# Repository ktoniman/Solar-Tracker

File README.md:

Electrical Engineering Principles and Practices (E1111A) Project
a Y1S1 project to be improved

If time allows, next pcb iteration using copper pours

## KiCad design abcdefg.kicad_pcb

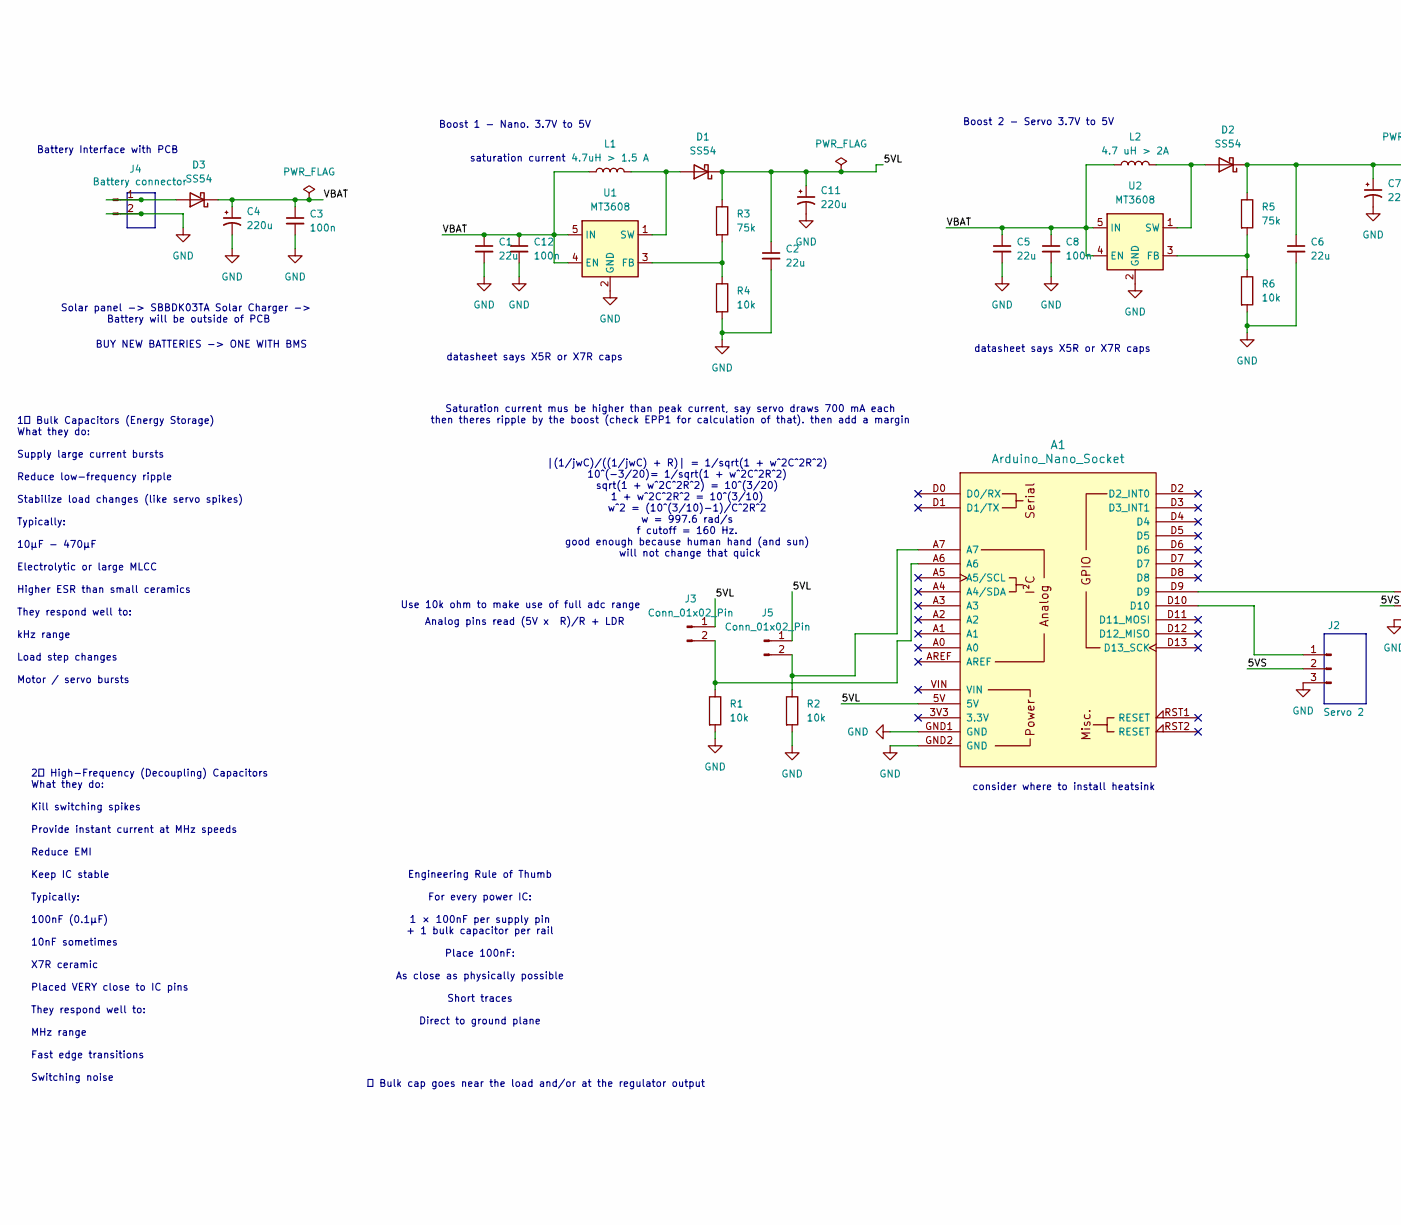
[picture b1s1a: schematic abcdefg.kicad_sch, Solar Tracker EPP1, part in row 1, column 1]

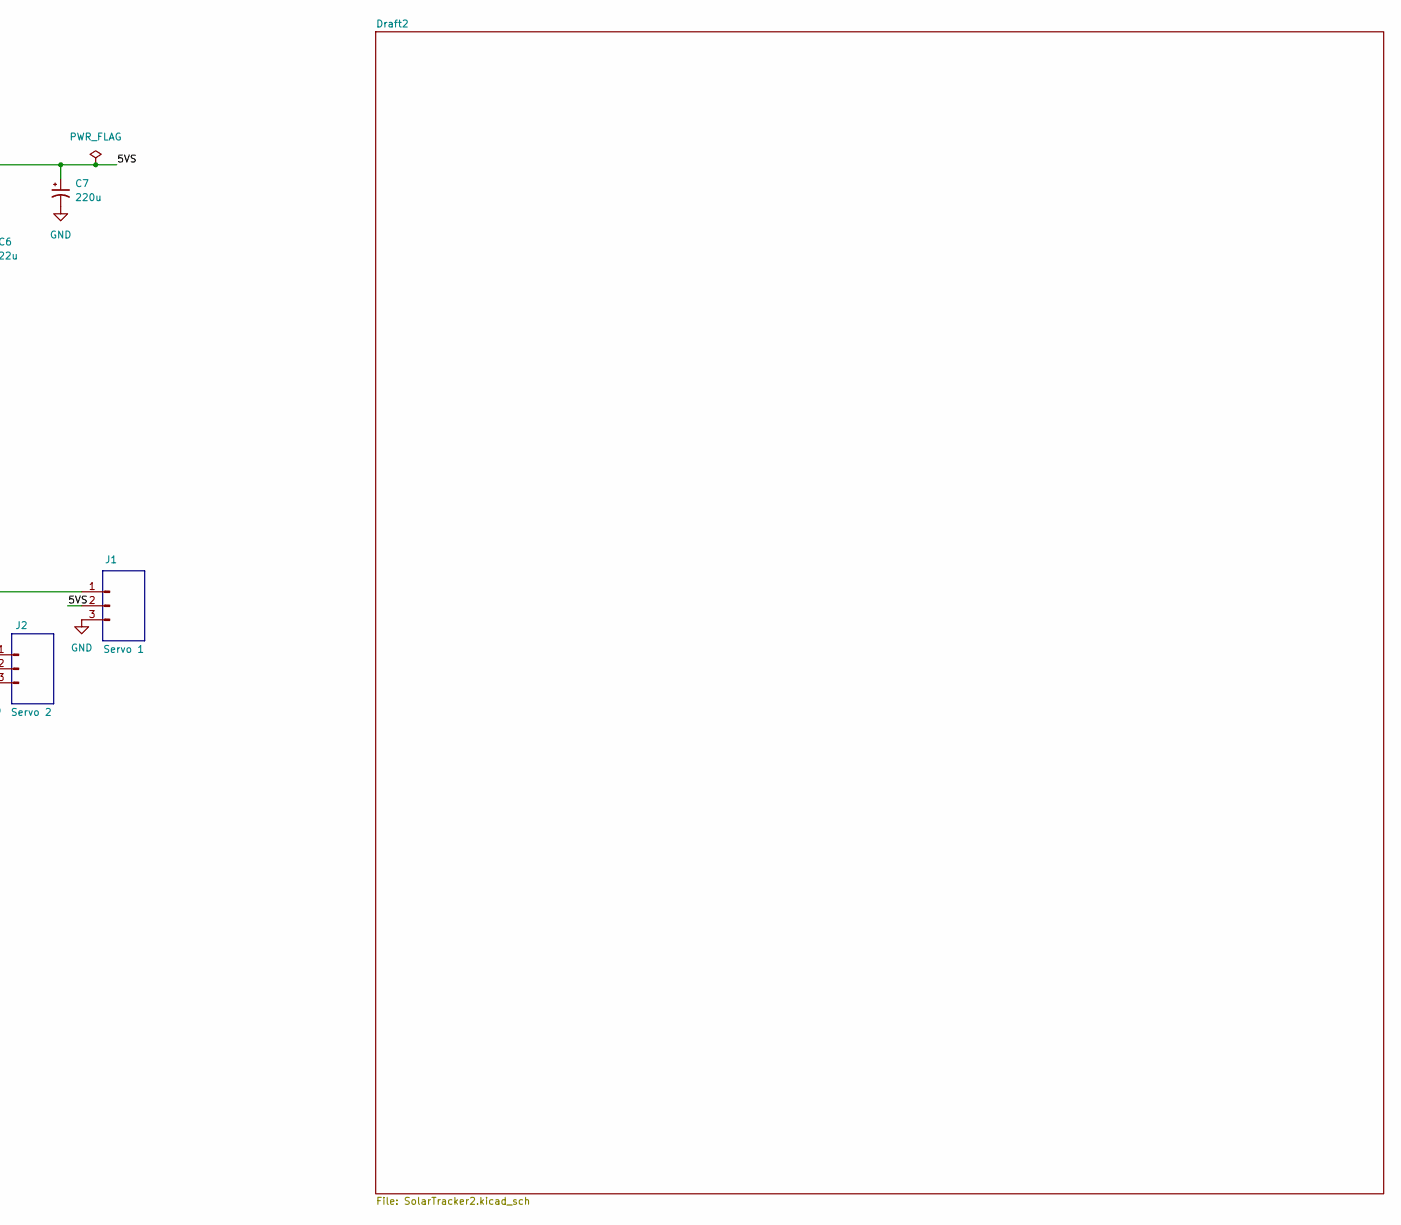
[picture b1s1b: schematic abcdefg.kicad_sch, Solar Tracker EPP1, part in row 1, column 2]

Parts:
A1: Arduino_Nano_Socket
C1, C2, C5, C6: 22u; C_0805_2012Metric
C3, C8, C12: 100n; C_0805_2012Metric
C4, C7, C11: 220u; CP_Elec_6.3x7.7
D1, D2, D3: SS54; D_SMA
J1: Servo 1; JST_XH_B3B-XH-A_1x03_P2.50mm_Vertical
J2: Servo 2; JST_XH_B3B-XH-A_1x03_P2.50mm_Vertical
J3, J5: Conn_01x02_Pin; JST_XH_B2B-XH-A_1x02_P2.50mm_Vertical
J4: Battery connector; JST_XH_B2B-XH-A_1x02_P2.50mm_Vertical
L1: 4.7uH > 1.5 A; L_Sunlord_SWPA8040S
L2: 4.7 uH > 2A; L_Sunlord_SWPA8040S
R1, R2, R4, R6: 10k; R_0805_2012Metric
R3, R5: 75k; R_0603_1608Metric
U1, U2: MT3608; SOT-23-6

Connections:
/5VL: A1.5V, C2.1, C11.1, D1.1 (K), J3.1, J5.1, R3.1
/5VS: C6.1, C7.1, D2.1 (K), J1.2, J2.2, R5.1
/VBAT: C1.1, C3.1, C4.1, C5.1, C8.1, C12.1, D3.1 (K), L1.1, L2.1, U1.4 (EN), U1.5 (IN), U2.4 (EN), U2.5 (IN)
GND: A1.GND1 (GND), A1.GND2 (GND), C1.2, C2.2, C3.2, C4.2, C5.2, C6.2, C7.2, C8.2, C11.2, C12.2, J1.3, J2.3, J4.2, R1.2, R2.2, R4.2, R6.2, U1.2 (GND), U2.2 (GND)
unnamed: D1.2 (A), L1.2, U1.1 (SW)
unnamed: D2.2 (A), L2.2, U2.1 (SW)
unnamed: D3.2 (A), J4.1
unnamed: A1.D9, J1.1
unnamed: A1.D10, J2.1
unnamed: A1.A6, J3.2, R1.1
unnamed: A1.A7, J5.2, R2.1
unnamed: R3.2, R4.1, U1.3 (FB)
unnamed: R5.2, R6.1, U2.3 (FB)

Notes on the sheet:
BUY NEW BATTERIES -> ONE WITH BMS
Solar panel -> SBBDK03TA Solar Charger -> Battery will be outside of PCB
Battery Interface with PCB
2️⃣ High-Frequency (Decoupling) Capacitors What they do: Kill switching spikes Provide instant current at MHz speeds Reduce EMI Keep IC stable Typically: 100nF (0.1µF) 10nF sometimes X7R ceramic Placed VERY close to IC pins They respond well to: MHz range Fast edge transitions Switching noise
1️⃣ Bulk Capacitors (Energy Storage) What they do: Supply large current bursts Reduce low-frequency ripple Stabilize load changes (like servo spikes) Typically: 10µF - 470µF Electrolytic or large MLCC Higher ESR than small ceramics They respond well to: kHz range Load step changes Motor / servo bur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
Use 10k ohm to make use of full adc range
Boost 2 - Servo 3.7V to 5V
datasheet says X5R or X7R caps
Saturation current mus be higher than peak current, say servo draws 700 mA each then theres ripple by the boost (check EPP1 for calculation of that). then add a margin
Analog pins read (5V x R)/R + LDR
saturation current
|(1/jwC)/((1/jwC) + R)| = 1/sqrt(1 + w^2C^2R^2) 10^(-3/20)= 1/sqrt(1 + w^2C^2R^2) sqrt(1 + w^2C^2R^2) = 10^(3/20) 1 + w^2C^2R^2 = 10^(3/10) w^2 = (10^(3/10)-1)/C^2R^2 w = 997.6 rad/s f cutoff = 160 Hz. good enough because human hand (and sun) will not change that quick
Engineering Rule of Thumb For every power IC: 1 × 100nF per supply pin + 1 bulk capacitor per rail Place 100nF: As close as physically possible Short traces Direct to ground plane
consider where to install heatsink
✅ Bulk cap goes near the load and/or at the regulator output
Boost 1 - Nano. 3.7V to 5V

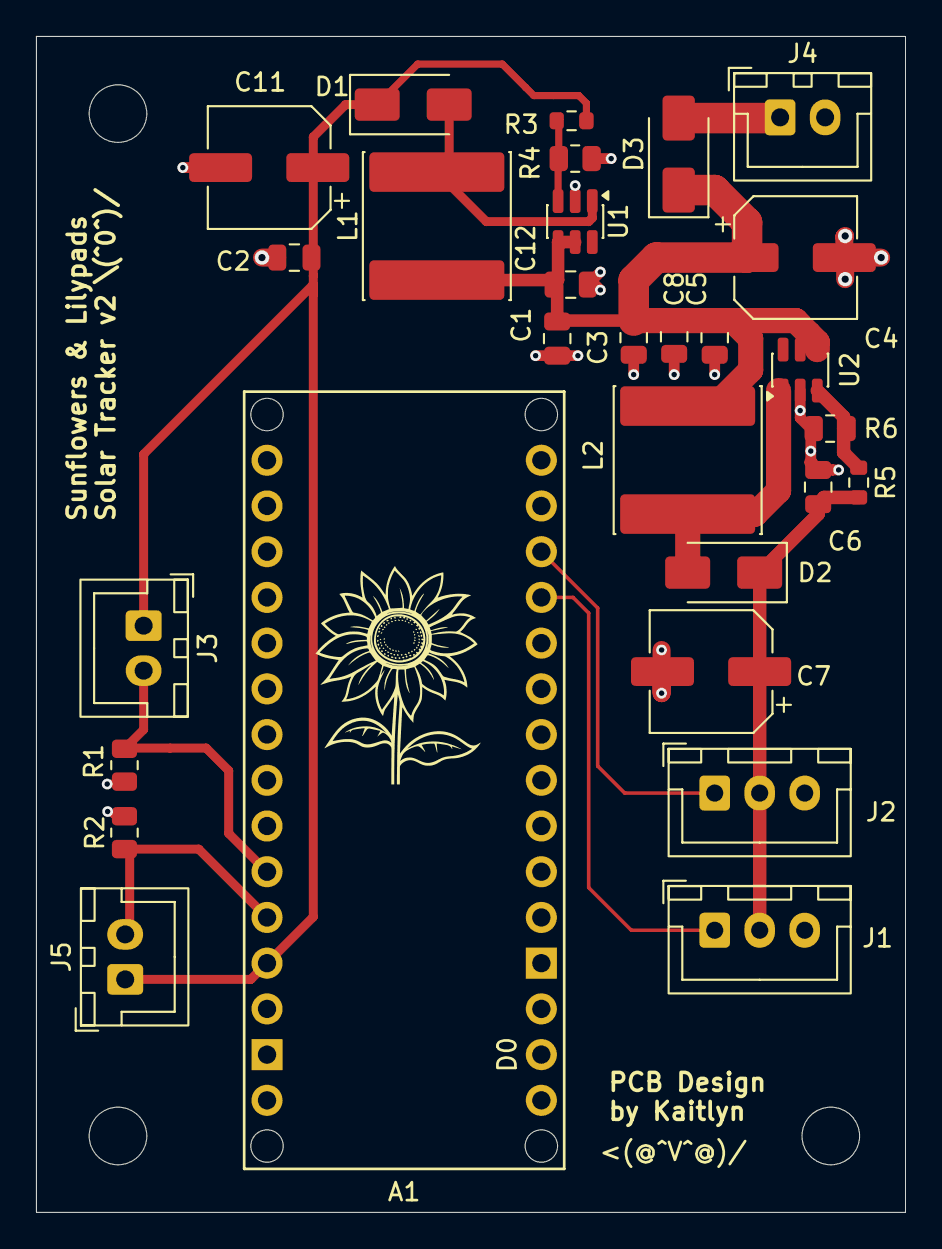
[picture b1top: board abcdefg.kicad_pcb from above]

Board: 2 copper layers, 48.3 x 65.3 mm, 29 parts (0 on the bottom side), 13 nets.

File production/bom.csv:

Designator,Footprint,Quantity,Value,LCSC Part #
A1,Arduino_Nano_Socket,1,Arduino_Nano_Socket,
"C1, C2, C5, C6",0805,4,22u,
"C11, C4, C7",CP_Elec_6.3x7.7,3,220u,
"C12, C3, C8",0805,3,100n,
"D1, D2, D3",D_SMA,3,SS54,
J1,JST_XH_B3B-XH-A_1x03_P2.50mm_Vertical,1,Servo 1,
J2,JST_XH_B3B-XH-A_1x03_P2.50mm_Vertical,1,Servo 2,
"J3, J5",JST_XH_B2B-XH-A_1x02_P2.50mm_Vertical,2,Conn_01x02_Pin,
J4,JST_XH_B2B-XH-A_1x02_P2.50mm_Vertical,1,Battery connector,
L1,L_Sunlord_SWPA8040S,1,4.7uH > 1.5 A,
L2,L_Sunlord_SWPA8040S,1,4.7 uH > 2A,
"R1, R2, R4, R6",0805,4,10k,
"R3, R5",0603,2,75k,
"U1, U2",SOT-23-6,2,MT3608,

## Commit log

2026-03-27 Put into files
2026-03-30 Updated PCB layout
2026-03-30 code uploaded
2026-03-30 BOM uploaded
2026-03-31 Traces made bigger, c2 moved, changed connectors
